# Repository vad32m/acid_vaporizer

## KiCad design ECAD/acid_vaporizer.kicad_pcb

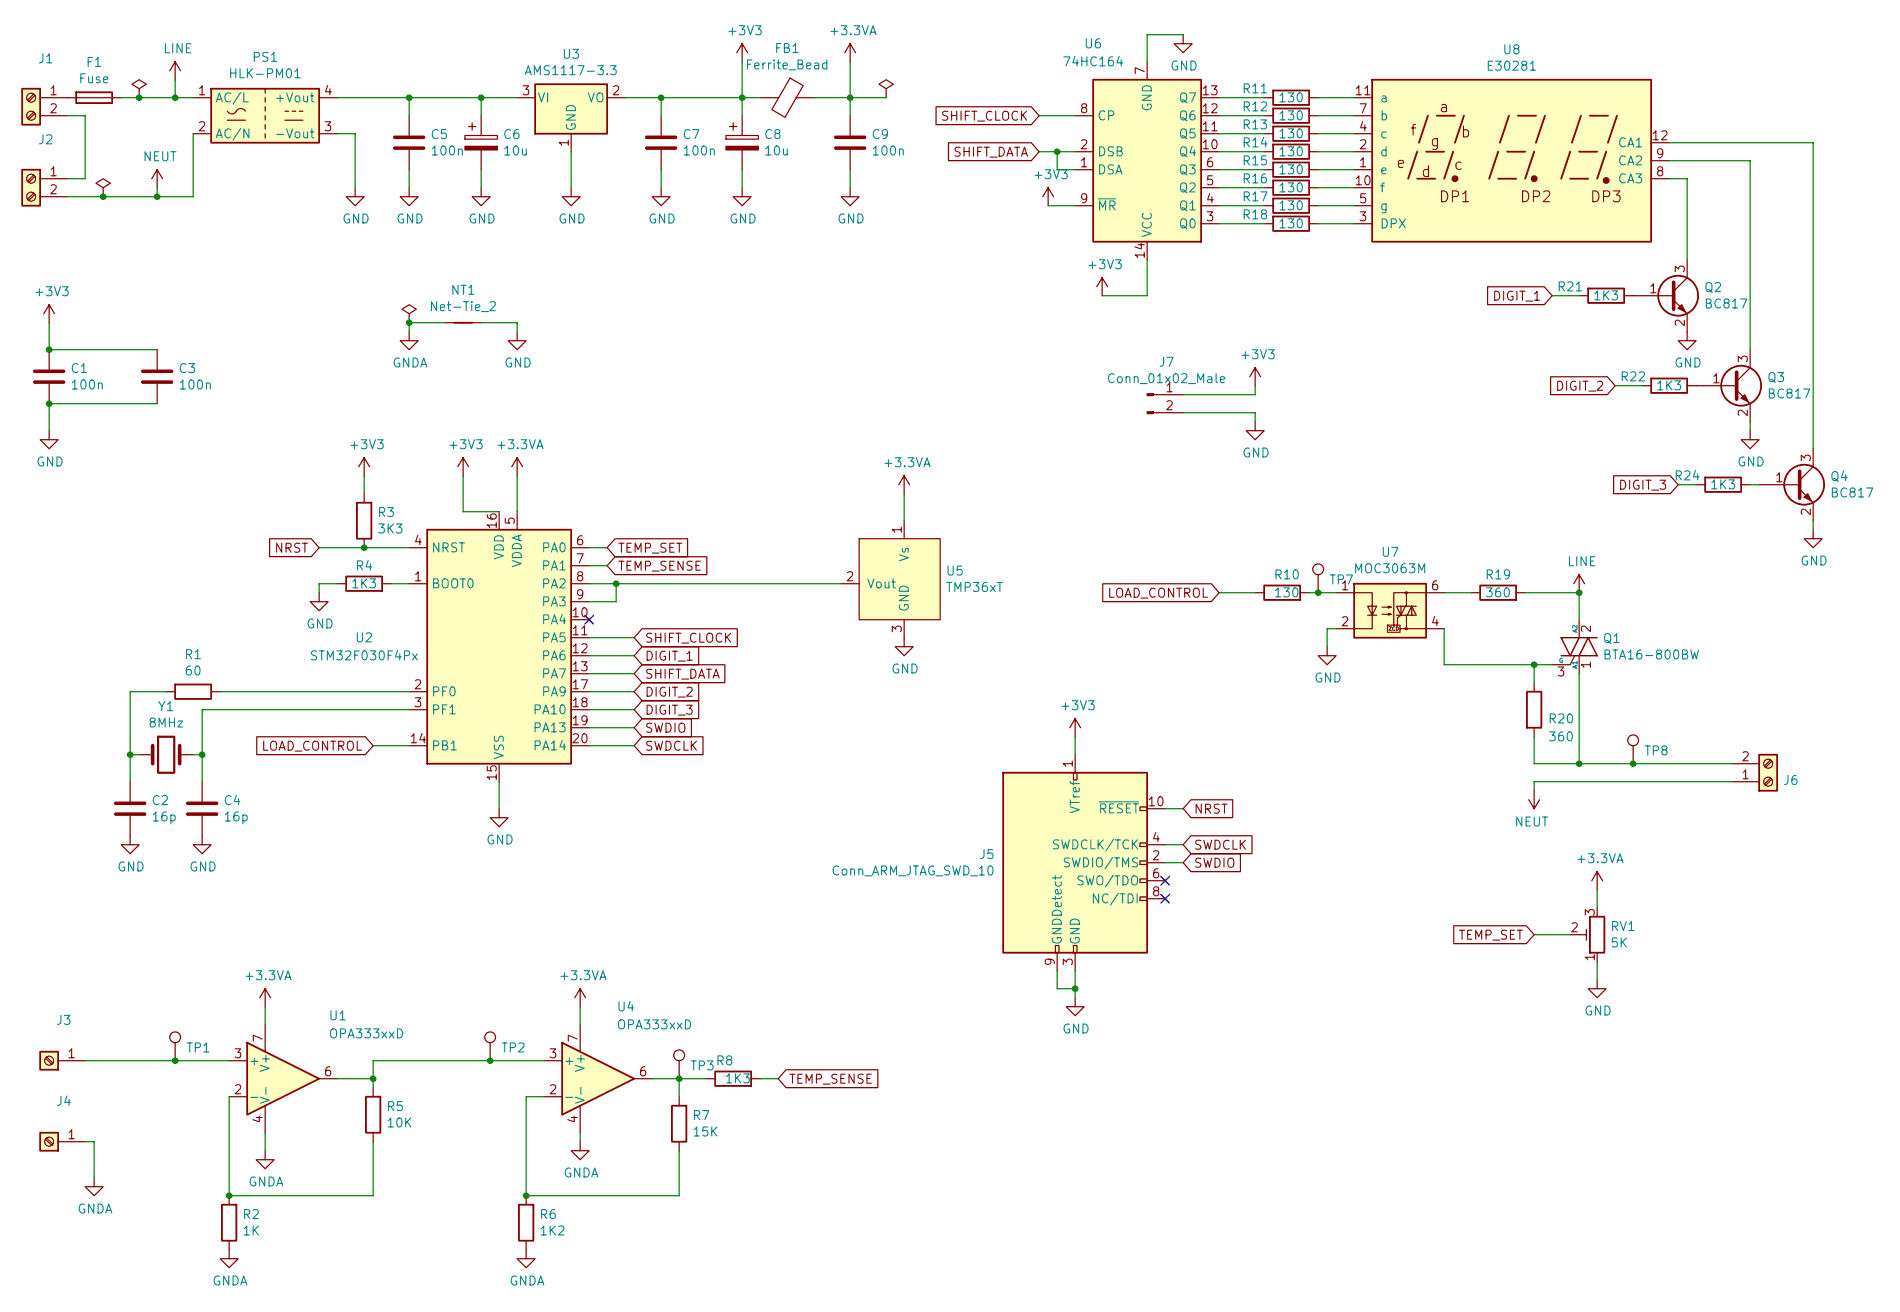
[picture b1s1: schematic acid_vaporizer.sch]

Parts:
C1, C3, C5, C7, C9: 100n; C_0805_2012Metric
C2, C4: 16p; C_0805_2012Metric
C6, C8: 10u; CP_Elec_4x5.3
F1: Fuse; FH5-1098
FB1: Ferrite_Bead; L_0603_1608Metric
J1, J2, J6: Screw_Terminal_01x02; TerminalBlock_1x02_P5.00mm_Horizontal
J3, J4: Screw_Terminal_01x01; K14-00(AH)
J5: Conn_ARM_JTAG_SWD_10; PinHeader_2x05_P1.27mm_Vertical
J7: Conn_01x02_Male; PinHeader_1x02_P2.54mm_Vertical
NT1: Net-Tie_2; NetTie-2_SMD_Pad0.5mm
PS1: HLK-PM01; HiLink_HLK-PMxx
Q1: BTA16-800BW; TO-220-3_Vertical
Q2, Q3, Q4: BC817; SOT-23
R1: 60; R_0805_2012Metric_Pad1.15x1.40mm_HandSolder
R2: 1K; R_0805_2012Metric_Pad1.15x1.40mm_HandSolder
R3: 3K3; R_0805_2012Metric_Pad1.15x1.40mm_HandSolder
R4, R8, R21, R22, R24: 1K3; R_0805_2012Metric_Pad1.15x1.40mm_HandSolder
R5: 10K; R_0805_2012Metric_Pad1.15x1.40mm_HandSolder
R6: 1K2; R_0805_2012Metric_Pad1.15x1.40mm_HandSolder
R7: 15K; R_0805_2012Metric_Pad1.15x1.40mm_HandSolder
R10, R11, R12, R13, R14, R15, R16, R17, R18: 130; R_0805_2012Metric_Pad1.15x1.40mm_HandSolder
R19: 360; R_Axial_DIN0207_L6.3mm_D2.5mm_P10.16mm_Horizontal
R20: 360; R_Axial_DIN0207_L6.3mm_D2.5mm_P7.62mm_Horizontal
RV1: 5K; Potentiometer_ACP_CA9-H2,5_Horizontal
TP1, TP2, TP3, TP7, TP8: TestPoint; TestPoint_Pad_1.5x1.5mm
U1, U4: OPA333xxD; SOIC-8_3.9x4.9mm_P1.27mm
U2: STM32F030F4Px; TSSOP-20_4.4x6.5mm_P0.65mm
U3: AMS1117-3.3; SOT-223-3_TabPin2
U5: TMP36xT; TO-92
U6: 74HC164; SOIC-14_3.9x8.7mm_P1.27mm
U7: MOC3063M; SMDIP-6_W9.53mm
U8: E30281
Y1: 8MHz; Crystal_HC49-4H_Vertical

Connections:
+3.3VA: C9.1, FB1.1, RV1.3, U1.7 (V+), U2.5 (VDDA), U4.7 (V+), U5.1 (Vs)
+3V3: C1.1, C3.1, C7.1, C8.1, FB1.2, J5.1 (VTref), J7.1, R3.2, U2.16 (VDD), U3.2 (VO), U6.9 (~MR), U6.14 (VCC)
DIGIT_1: R21.2, U2.12 (PA6)
DIGIT_2: R22.2, U2.17 (PA9)
DIGIT_3: R24.2, U2.18 (PA10)
GND: C1.2, C2.2, C3.2, C4.2, C5.2, C6.2, C7.2, C8.2, C9.2, J5.3 (GND), J5.5 (GND), J5.9 (GNDDetect), J7.2, NT1.2, PS1.3 (-Vout), Q2.2 (E), Q3.2 (E), Q4.2 (E), R4.1, RV1.1, U2.15 (VSS), U3.1 (GND), U5.3 (GND), U6.7 (GND), U7.2
GNDA: J4.1, NT1.1, R2.1, R6.1, U1.4 (V-), U4.4 (V-)
LINE: F1.1, PS1.1 (AC/L), Q1.2 (A2), R19.2
LOAD_CONTROL: R10.1, U2.14 (PB1)
NEUT: J2.2, J6.1, PS1.2 (AC/N)
NRST: J5.10 (~RESET~), R3.1, U2.4 (NRST)
unnamed: C2.1, R1.2, Y1.1
unnamed: C4.1, U2.3 (PF1), Y1.2
unnamed: C5.1, C6.1, PS1.4 (+Vout), U3.3 (VI)
unnamed: F1.2, J1.1
unnamed: J1.2, J2.1
unnamed: J3.1, TP1.1, U1.3 (+)
unnamed: J6.2, Q1.1 (A1), R20.2, TP8.1
unnamed: Q1.3 (G), R20.1, U7.4
unnamed: Q2.1 (B), R21.1
unnamed: Q2.3 (C), U8.8 (CA3)
unnamed: Q3.1 (B), R22.1
unnamed: Q3.3 (C), U8.9 (CA2)
unnamed: Q4.1 (B), R24.1
unnamed: Q4.3 (C), U8.12 (CA1)
unnamed: R1.1, U2.2 (PF0)
unnamed: R2.2, R5.1, U1.2 (-)
unnamed: R4.2, U2.1 (BOOT0)
unnamed: R5.2, TP2.1, U1.6, U4.3 (+)
unnamed: R6.2, R7.1, U4.2 (-)
unnamed: R7.2, R8.1, TP3.1, U4.6
unnamed: R10.2, TP7.1, U7.1
unnamed: R11.1, U8.11 (a)
unnamed: R11.2, U6.13 (Q7)
unnamed: R12.1, U8.7 (b)
unnamed: R12.2, U6.12 (Q6)
unnamed: R13.1, U8.4 (c)
unnamed: R13.2, U6.11 (Q5)
unnamed: R14.1, U8.2 (d)
unnamed: R14.2, U6.10 (Q4)
unnamed: R15.1, U8.1 (e)
unnamed: R15.2, U6.6 (Q3)
unnamed: R16.1, U8.10 (f)
unnamed: R16.2, U6.5 (Q2)
unnamed: R17.1, U8.5 (g)
unnamed: R17.2, U6.4 (Q1)
unnamed: R18.1, U8.3 (DPX)
unnamed: R18.2, U6.3 (Q0)
unnamed: R19.1, U7.6
unnamed: U2.8 (PA2), U2.9 (PA3), U5.2 (Vout)
SHIFT_CLOCK: U2.11 (PA5), U6.8 (CP)
SHIFT_DATA: U2.13 (PA7), U6.1 (DSA), U6.2 (DSB)
SWDCLK: J5.4 (SWDCLK/TCK), U2.20 (PA14)
SWDIO: J5.2 (SWDIO/TMS), U2.19 (PA13)
TEMP_SENSE: R8.2, U2.7 (PA1)
TEMP_SET: RV1.2, U2.6 (PA0)

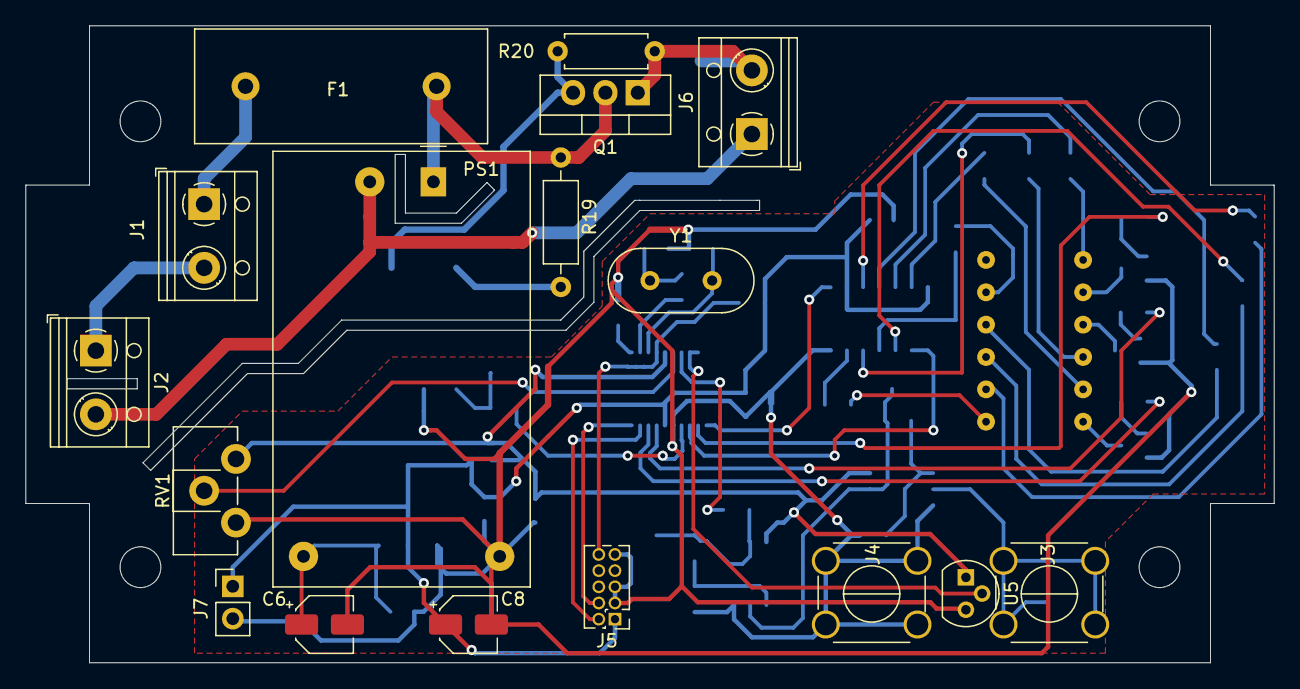
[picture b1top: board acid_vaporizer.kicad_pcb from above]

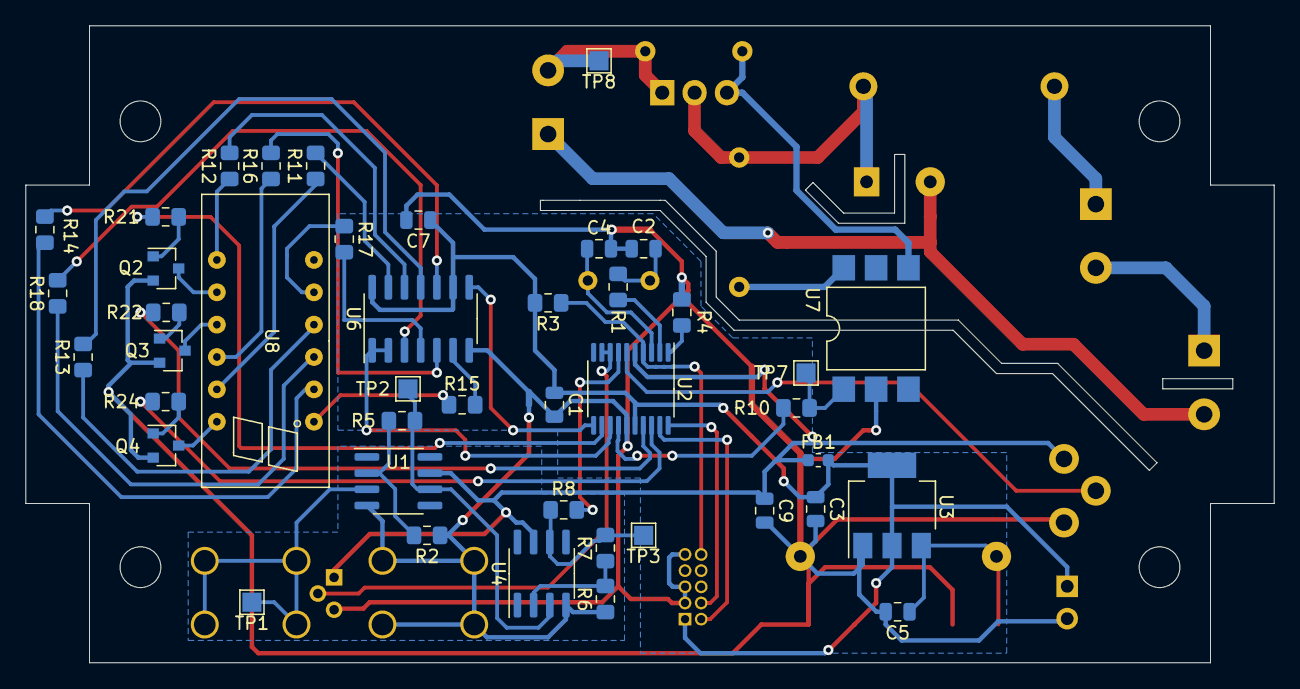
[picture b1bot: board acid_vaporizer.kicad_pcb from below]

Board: 2 copper layers, 98.0 x 50.0 mm, 61 parts (44 on the bottom side), 56 nets.

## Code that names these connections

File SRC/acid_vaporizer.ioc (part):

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Mcu.Name=STM32F030F4Px
Mcu.Package=TSSOP20
Mcu.UserName=STM32F030F4Px
PA0.Mode=IN0
PA0.Signal=ADC_IN0
PA1.Mode=IN1
PA1.Signal=ADC_IN1
PA10.Signal=GPIO_Output
PA13.Mode=Serial_Wire
PA13.Signal=SYS_SWDIO
PA14.Mode=Serial_Wire
PA14.Signal=SYS_SWCLK
PA2.Mode=IN2
PA2.Signal=ADC_IN2
PA3.Mode=IN3
PA3.Signal=ADC_IN3
PA5.Mode=TX_Only_Simplex_Unidirect_Master
PA5.Signal=SPI1_SCK
PA6.Signal=GPIO_Output
PA7.Mode=TX_Only_Simplex_Unidirect_Master
PA7.Signal=SPI1_MOSI
PA9.Signal=GPIO_Output
PB1.Signal=S_TIM3_CH4
PF0-OSC_IN.Mode=HSE-External-Oscillator
PF0-OSC_IN.Signal=RCC_OSC_IN
PF1-OSC_OUT.Mode=HSE-External-Oscillator
PF1-OSC_OUT.Signal=RCC_OSC_OUT
RCC.SYSCLKFreq_VALUE=16000000
RCC.SYSCLKSource=RCC_SYSCLKSOURCE_PLLCLK
board=custom

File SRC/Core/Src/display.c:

/*
 * display.c
 *
 *  Created on: Mar 14, 2021
 *      Author: vadym.mishchuk
 */
//		 A
//	  _______
//   |       |
// F |       | B
//	 |  G    |
//	 ---------
//	 |       |
// E |       | C
//	 |       |
//	 ---------    ----
//		D        | DP |
//                ----

#include <stdint.h>
#include <stdbool.h>

#include "stm32f0xx_ll_gpio.h"
#include "stm32f0xx_ll_spi.h"
#include "stm32f0xx_ll_tim.h"

#define DIGITS 3

#define SEG_A  0x80
#define SEG_B  0x40
#define SEG_C  0x20
#define SEG_D  0x10
#define SEG_E  0x08
#define SEG_F  0x04
#define SEG_G  0x02
#define SEG_DP 0x01

#define DIGIT_0  (SEG_A | SEG_B | SEG_C | SEG_D | SEG_E | SEG_F)
#define DIGIT_1  (SEG_B | SEG_C)
#define DIGIT_2  (SEG_A | SEG_B | SEG_G | SEG_E | SEG_D)
#define DIGIT_3  (SEG_A | SEG_B | SEG_G | SEG_C | SEG_D)
#define DIGIT_4  (SEG_F | SEG_B | SEG_G | SEG_C)
#define DIGIT_5  (SEG_A | SEG_F | SEG_G | SEG_C | SEG_D)
#define DIGIT_6  (SEG_A | SEG_F | SEG_G | SEG_C | SEG_D | SEG_E)
#define DIGIT_7  (SEG_A | SEG_B | SEG_C)
#define DIGIT_8  (SEG_A | SEG_B | SEG_C | SEG_D | SEG_E | SEG_F | SEG_G)
#define DIGIT_9  (SEG_A | SEG_B | SEG_C | SEG_D | SEG_F | SEG_G)

#define SYMBOL_E  (SEG_A | SEG_D | SEG_E | SEG_F | SEG_G)
#define SYMBOL_r  (SEG_E | SEG_G)

static const uint8_t digitBitmaps[] = {
		DIGIT_0,
		DIGIT_1,
		DIGIT_2,
		DIGIT_3,
		DIGIT_4,
		DIGIT_5,
		DIGIT_6,
		DIGIT_7,
		DIGIT_8,
		DIGIT_9};

static const uint32_t digitEnablePins[DIGITS] = {
		LL_GPIO_PIN_6,
		LL_GPIO_PIN_9,
		LL_GPIO_PIN_10
};

static uint8_t digits[DIGITS];

static uint8_t currentDigitIdx = 0;

static bool isBlinking = false;

void TIM14_IRQHandler(void)
{
	static bool displayOn;
	static uint8_t ticks;

	LL_GPIO_ResetOutputPin(GPIOA, digitEnablePins[currentDigitIdx]);

	//blink once in a second
	ticks = (ticks + 1) % 250;

	//duty cycle is 50% - 0.5 sec on and 0.5 sec off
	if (ticks == 0) {
		displayOn = true;
	} else if (ticks == 125) {
		displayOn = false;
	}

	if (!isBlinking || displayOn)
	{
		currentDigitIdx = (currentDigitIdx + 1) % DIGITS;
		LL_SPI_TransmitData8(SPI1, digits[currentDigitIdx]);
		LL_GPIO_SetOutputPin(GPIOA, digitEnablePins[currentDigitIdx]);
	}

	LL_TIM_ClearFlag_UPDATE(TIM14);
}

void DISPLAY_Init(void)
{
	LL_SPI_Enable(SPI1);
	LL_SPI_SetBaudRatePrescaler(SPI1, LL_SPI_BAUDRATEPRESCALER_DIV8);

	LL_TIM_SetClockSource(TIM14, LL_TIM_CLOCKSOURCE_INTERNAL);
	//timer will be counting on 10 kHz frequency
	LL_TIM_SetPrescaler(TIM14, 1600 - 1);
	//timer IRQ will be generated each 4 ms (250 kHz frequency)
	LL_TIM_SetAutoReload(TIM14, 40 - 1);
	LL_TIM_SetCounterMode(TIM14, LL_TIM_COUNTERMODE_UP);
	LL_TIM_EnableUpdateEvent(TIM14);
	LL_TIM_EnableIT_UPDATE(TIM14);
	LL_TIM_EnableCounter(TIM14);

	NVIC_EnableIRQ(TIM14_IRQn);

}

void DISPLAY_SetNumber(uint16_t number)
{
	if (number > 999)
	{
		number = 999;
	}

	for (uint8_t Idx = 0; Idx < DIGITS; Idx++)
	{
		uint8_t CurrentDigit = number % 10;
		digits[Idx] = digitBitmaps[CurrentDigit];
		number = number / 10;
	}
}

void DISPLAY_SetError(void)
{
	digits[2] = SYMBOL_E;
	digits[1] = SYMBOL_r;
	digits[0] = SYMBOL_r;
}

void DISPLAY_StartBlinking(void)
{
	isBlinking = true;
}

void DISPLAY_StopBlinking(void)
{
	isBlinking = false;
}

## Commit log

2020-11-08 Add .gitignore
2020-11-08 Add initial version of schematic and PCB
2020-11-08 Add initial mechanical design version
2020-12-29 Add firmware project skeleton
2021-03-20 Configure hardware timers for triac and display control
2021-03-20 Add initial implementation of display driver
2021-03-21 Add "blinking" functionality to display driver
2021-03-21 Add ability to show "ERr string on display"
2021-03-28 Schematic and PCB: replasce DS18B20 by TMP36
2021-03-28 Change configuration to read data from analog temperature senseor
2021-04-03 Add initial implementation for ADC module that reads sensors
2021-04-04 Add translation from voltages to units for sensors
2021-04-06 Add module for controlling PWM output
2021-04-09 Add timer callback for updating load control in sync with PWM
2021-04-30 Add code of PI controller
2021-04-30 Integrate PI contoller into project
2021-04-30 Add images of PCB and device in enclosure
